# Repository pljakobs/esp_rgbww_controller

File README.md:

View this project on [CADLAB.io](https://cadlab.io/project/1422). 

# ESP8266 WiFi RGBWW LED Dimmer v1.5
Custom Hardware board for controlling 5 Led Channels via PWM (RGB + Warm/Cold White). It is designed for max current ~4.5A per Channel.

# Changelog

* 1.5 (31.01.2017)
  * DCDC wandler has been remeasured and provided for through hole mounting on pin headers
  * Jumper introduced for allowing for external 3,3V connections
  * measurements have been changed to 53mm*47mm with mounting holes tailored towards "Strapubox CO 4" casing
  * C1 has been replaced with a smaller form factor

* 1.3 (20.02.2016)
  * added another tact switch which can be used during boot to reset settings
  * silksceen naming updated 

* 1.2 (16.02.2016)
  * improved the layout for better EMV
  * added buffer capacitor for dc converter
  * added filter capacitor close to ESP8266
  
* 1.1 (01.02.2016)
  * connected ADC 
  * some layout improvements

# Parts
- 1x ESP8266, ESP-12 format
- 1x XM1584 Power converter (set to 3.3v!)
- 5x IRLZ44N Mosfet (logic level gate threshold)
- 11x 10k resistors, 0805 (R1 - R11)
- 1x 1k resistors, 0805 (R12)
- 1x 330 µF Elko RM 2.5 mm (C1) 
- 1x 100 µF Elko RM 2.5 mm (C3)
- 1x 100 nF capacitor 0805(C2)
- 3x 5,08mm 2pin terminal block
- 1x 5,08mm 3pin terminal block
- 1x 2,54mm 4pin header
- 2x Micro SMD Tact Switch 2 pin 3*6*2.5 mm (optional)

# Assembly
Assembly of the PCB Board is straight forward, solder all parts to the PCB.

__Caution :__ before soldering the esp module to the PCB, set the output voltage of XM1584 converter  to 3.3v

### Recommended steps
- Start with soldering the smd resistors
- __Ensure the output voltage of XM1584 converter is 3.3v before continuing__. 
- Solder the XM1584 Power Board 
- Solder ESP8266 Module 
- Optional: solder SMD Tact Switch
- Solder Elkos
- Solder Terminal Blocks, 4pin header 
- Solder FETs

# Firmware
Firmware is still work in progress.

Latest can be found here:
https://github.com/patrickjahns/esp_rgbww_controller_fw

# Modifying
The schematic and board files are compatible with eagle 7.2+

## Ideas
Here are some ideas for future revisions
- see if we can clear some GPIOs and provide them via PIN Header for other enhancements (i.e. IR / Rotary Controller) 
- change layout for VCC/GND to be on the left side
- ~~connect ADC to detect power failure~~ 

# Resources
* [ESP RGB Project](https://github.com/RiRomain/esp-dimmer-hardware)
* [H801 Wifi Controller Hack](http://chaozlabs.blogspot.de/2015/08/esp8266-in-wild-wifi-led-controller-hack.html)

# Thread in Fhem Forum
* [Entwicklung/Sammelbestellung RGBWW Wifi Led Controller](https://forum.fhem.de/index.php/topic,48918.msg)

# Credits
Thanks to RiRomain for his excellent documentated [ESP RGB Project](https://github.com/RiRomain/esp-dimmer-hardware)

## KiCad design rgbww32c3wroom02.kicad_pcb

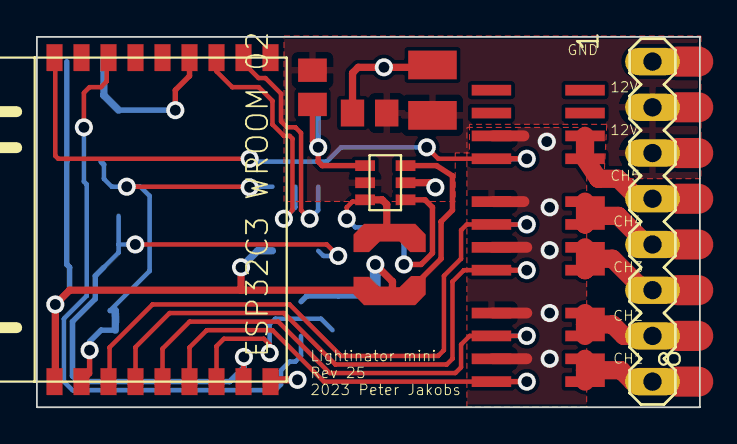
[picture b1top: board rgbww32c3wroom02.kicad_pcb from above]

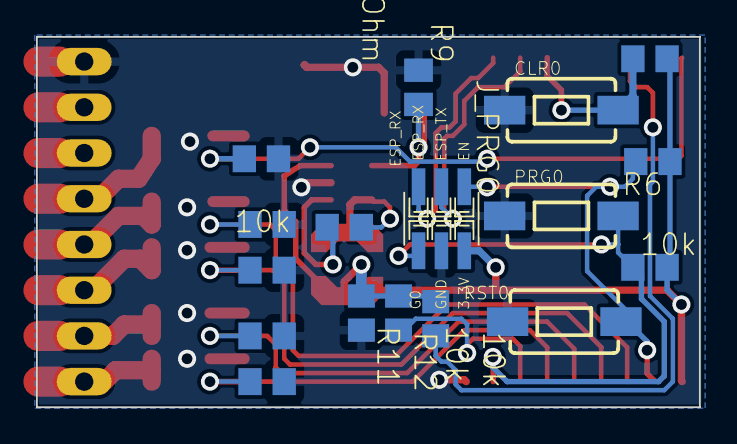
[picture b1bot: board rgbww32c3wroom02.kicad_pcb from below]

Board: 2 copper layers, 36.8 x 20.6 mm, 27 parts (17 on the bottom side), 23 nets.

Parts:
C3: 4.7µF; C1210
C4, C6: 100nF; C0805
C5: 22µF; C0805
CLR0: TACTILE-SWITCH-1101NE
J_PRG0: 1296-T06; 06
L1: 15µH; LPS4018
PRG0: TACTILE-SWITCH-1101NE
R1, R2, R3, R4, R5, R6, R7, R10, R11, R12: 10k; R0805
R8: 412kOhm; M0805
R9: 200kOhm; M0805
RST0: TACTILE-SWITCH-1101NE
SV1: MA08-1
U$1, U$2, U$3: AOD4806; SO08
U$5: ESP32C3WROOM02; SMD
U$6: TPS5604030; SOT23-6

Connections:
3V3: C5.1, J_PRG0.2, L1.2, R6.1, R7.2, R10.1, R11.2, R12.2, U$5.P$9, U$6.3
12V: C3.1, C4.1, R8.2, SV1.2, SV1.3, U$6.5
BOOT: C6.1, U$6.1
CH1: SV1.8, U$1.5, U$1.6
CH1A: R4.1, U$1.4, U$5.P$4
CH2: SV1.7, U$1.7, U$1.8
CH2A: R3.1, U$1.2, U$5.P$5
CH3: SV1.6, U$2.5, U$2.6
CH3A: R2.1, U$2.4, U$5.P$6
CH4: SV1.5, U$2.7, U$2.8
CH4A: R5.1, U$2.2, U$5.P$7
CH5: SV1.4, U$3.5, U$3.6
CH5A: R1.2, U$3.4, U$5.P$18
CLR: CLR0.2, R10.2, U$5.P$13
EN: J_PRG0.1, R6.2, RST0.2, U$5.P$8
EN_P: R8.1, R9.2, U$6.4
GND: C3.2, C4.2, C5.2, CLR0.1, J_PRG0.4, PRG0.1, R1.1, R2.2, R3.2, R4.2, R5.2, R9.1, RST0.1, SV1.1, U$1.1, U$1.3, U$2.1, U$2.3, U$3.3, U$5.P$1, U$6.2
IO2: R12.1, U$5.P$16
IO8: R11.1, U$5.P$3
PRG: J_PRG0.6, PRG0.2, R7.1, U$5.P$2
RX: J_PRG0.5, U$5.P$11
SW: C6.2, L1.1, U$6.6
TX: J_PRG0.3, U$5.P$12

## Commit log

2017-10-04 new, smaller board
    new design, integrated DCDC converter, new, smaller MOSFETs, smaller overal board, additional PRG button, mostly optimized for SMD manufacturing but still hand solderable
2017-11-19 minor placement changes
2017-11-19 another reduction in size
    replaced most of the power supply parts, shaved off another 3mm
2018-03-01 updated silk screen
    some minor changes, mostly cleaned up silk screen
2018-03-01 added BOM
    BOM
2018-04-07 added enable function
    I added a pin header to short the TPS5410's ENABLE pin to GND, thus switching off the DC/DC converter, effectively turning the controller completely off.
    The controller should function normally, when this is left open. Including a switch that connects those two pins is a way of switching the controller off without disconnecting the 12V supply. Whateve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
2018-04-11 some power supply improvements
    added a snubber network to PH (140MHz) plus a 10nF cap on the +3V3 line
    Added low impedance floodfills for +3V3 and PH where applicable
    switched the location of the RST and PRG switches since it seems easier to have the RST on the outside
2018-04-14 more board improvements
    - floodfills for VCC, PH and top layer +3V3 nods
    - RC snubber for PH node
    - additional 10nF cap close to the ESPs 3.3V
    - cleaned up the GND layer a bit
2018-05-05 yet more minor changes on the input side
    removed the snubber pads
    created a lower impedance GND path
    swiched RXD and TXD for some more elegant routing and better fit with the usual USB/UART connectors (straight cable now switches RX/TX)
    minor silkscreen corrections for better legibility
2018-05-12 updated Gerber Files and Pictures
    exported Gerber Files, shot a few new pictures of the board.
    Unlike the Beta Boards, this version does not have pads for an R/C snubber as I don't think it will be necessary. Also, there's a larger GND area covering the top layer input side of the circuit and 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
    The TXD and RXD pins have switched places, it was easier to route them like that and also, their location now crosses over with the usual USB/UART converters (straight cable run).
    On the disable jumper location, the pins have also switched places, disable is now on the top, pointing away from C3
2018-05-12 added two dimension measurements
2018-05-12 cosmetical correction
    beautified the crossing of RXD and TXD
2018-09-13 minor routing changes
    updated a few minor routings (clr) and added some more copper areas (GND around DISABLE & D1)
2018-11-14 Backlink to CADLAB.io has been added.
2018-11-15 fixed a pretty embarassing error
    I had one ground trace clip one of the PWM output pads.
2018-11-21 minor change
    one of the GND traces (between R2 and R3) underneath the top ground plane was not connected - doesn't make a change in the final board since it's one copper layer anyway.
2018-12-01 added six pin connector for programming
    changed the three pin programming header to a six pin version, allowing to directly plug in one of the universal FTDI based USB to UART adaptors.
    Pinout is:
    1: GND
    2: NC
    3: NC
    4: RX
2018-12-01 created a bit more room for a sliding mount by moving the decoupling caps C2 and C5 in a bit.
2019-01-27 minor changes
    increased the size of the button text
    very minor re-route of GPIO2 to resistor
2019-02-03 updated gerber files
2019-02-04 added three accessible GPIOs
    Added header pins for GPIOS 0,2 and 16 (which are all pulled high on board).
    If using Tasmota, or if we make changes to the "native" firmware, those can be used to signal via MQTT and thus to provide "local" control
2019-02-04 minor update
    moved one signal in the schematic, no electrical change
2019-02-04 minor corrections
    mainly values to make sure the BOM is all right
2019-02-16 small changes
2019-02-27 Update esp12_RGBWW.sch
    I had added and removed a power jack.
2019-03-13 small silkscreen changes
2019-03-13 added fhem logo and reference
2019-10-06 final production version
2019-11-08 added VCC and G15 to pin header
    in the earlier design, I had omitted a VCC pin at the pin header. That could be a useful pin for folks using the board with the TAMSOTA firmware, opening up a few pins for external sensors.
    Now G0, G2, G15 and G16 are available on the header.
    When using them, you should be aware that G0, G2 and G16 are internally pulled up and G15 is pulled low. depending on the loaded firmware, changing the level of those pins (especially at boot time) m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
2025-04-18 commitintg the Lightinator mini design in Eagle format
2025-04-18 initial kicad versions
2025-04-18 project changes by opening it on linux for the first time
